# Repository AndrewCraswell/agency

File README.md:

# Agency monorepo

A Turborepo and pnpm monorepo for the agency's applications and shared packages.

## What's inside?

This Turborepo includes the following packages and apps:

### Apps and Packages

- `blog-writer`: Shopify blog-writing application
- [legislation-web](apps/legislation-web/README.md): browser product, public HTTP API and query runtime
- [legislation-ingestion](apps/legislation-ingestion/README.md): source acquisition, workers and indexing
- [legislation-mcp](apps/legislation-mcp/README.md): standalone authenticated MCP-to-HTTP adapter
- [@repo/legislation-core](packages/legislation-core/README.md): shared contracts, database schema and primitives
- `scoring`: fencing scoring application and supporting tools
- `@repo/oxlint-config`: shared [oxlint](https://oxc.rs) configuration
- `@repo/storybook-config`: shared [Storybook](https://storybook.js.org) configuration
- `@repo/typescript-config`: `tsconfig.json`s used throughout the monorepo

Applications and shared packages primarily use [TypeScript](https://www.typescriptlang.org/); legislation ingestion also
owns Python parser and scraper runtimes.

### Install dependencies

Some workspaces use `@1js` packages from the Office Azure Artifacts feed. Install dependencies normally:

```sh
pnpm install
```

If installation fails because the feed credentials have expired, refresh them and retry:

```sh
pnpm auth
pnpm install
```

For legislation setup, including local credentials after the workspace moves, see the
[runtime guide](apps/legislation-web/docs/operations/development.md). From the repository root,
`pnpm verify:legislation` runs the five-package legislation verification suite, including the diffing package.
`pnpm verify` currently delegates to that same legislation-only gate; it is not a full monorepo check. Database release
commands are owned by web and delegate to core.

### Utilities

This Turborepo has some additional tools already setup for you:

- [TypeScript](https://www.typescriptlang.org/) for static type checking
- [oxlint](https://oxc.rs) for code linting
- [oxfmt](https://oxc.rs) for code formatting
- [Vitest](https://vitest.dev) for testing
- [Lefthook](https://lefthook.dev) for Git hooks

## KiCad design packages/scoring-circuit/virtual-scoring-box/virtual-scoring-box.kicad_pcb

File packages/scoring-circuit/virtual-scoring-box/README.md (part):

# Virtual scoring box

Open `virtual-scoring-box.kicad_pro` in KiCad 10. This separate development PCB is routed and has an assembly-review
export; it has not been released to a manufacturer. The combined `../usb-scoring-platform/` design is frozen at commit
`ea7c3af023e6ad69eb4b2c7591a94a8ba3619fca`; do not change it while developing this board. Its supplier draft remains
paused.

## Product boundary

- STM32 determines foil, epee and sabre touches. The laptop displays results and controls the bout; network arrival time
  never determines contact timing. Timestamped conductor events may also be exported for development and diagnostics.
- ESP32 handles Wi-Fi/Bluetooth connectivity and the same IR remote as the future standalone model. Both processors must
  be powered in USB and wireless operation. Share firmware source and the C17 scoring core, with board-specific
  configuration.
- One USB-C port provides laptop power/data or wall-charger power for wireless use. Retain the adequately powered USB-C
  source requirement; universal USB-A adapter operation is not promised.
- Left and right enclosure-mounted ABC sockets connect by soldered wires to opposite sides of the PCB. The piste socket
  also connects by soldered wire. Provide strain relief; the piste reference is not protective earth.
- Retain accessible STM32 SWD and ESP32 programming/recovery interfaces. Same update approach as the standalone product.
- No Ethernet, Favero outputs, HUB75, audio, or high-power display supply.

## Current state and next work

The schematic contains the two acquisition circuits, STM32, ESP32, input reset-default resistors, TSOP38438 IR receiver,
and a USB-C data interface. Twenty-two standalone-only processor connections have been replaced with explicit
no-connects. J3/J4/J5 are bare PCB wire-solder terminations, excluded from the purchased-parts BOM; their provisional
1.2mm drills and wire strain relief still need assembly review. Unused copied custom symbols and header footprints have
been removed.

The native PCB has **146 footprints**, including **142 purchased components**, on a **120 x 85mm, four-layer, 1.6mm**
board. The USB interface uses GCT USB4105-GF-A, TPD2E2U06DCKR protection, a **CP2102N-A02-GQFN20R USB-to-UART bridge**,
and an **ISO7021DR serial isolator**. **TPS70933DBVR** supplies the laptop-side 3.3V rail and tolerates raw VBUS up to
30V. Its EN pin is intentionally open using the internal pull-up, never connected directly to high-voltage VBUS. C40 is
4.7uF.

`usb-power-control.kicad_sch` adds **STUSB4500QTR**, **STM32C011F6P6** and **TPS259470ARPWR**. Program and read back a
single **5V / 1.5A sink PDO** after delivery, before normal use. The eFuse provides automatic-retry current limiting,
reverse-current blocking and adjustable voltage protection. R85 sets approximately 1.21A; C54 gives approximately 25ms
for the 5V ramp. ITIMER is intentionally open for the fastest overcurrent response. Nominal UVLO is 4.04V rising / 3.69V
falling; nominal OVLO is 5.38V rising / 4.91V falling. Divider resistors are 0.1%; temperature, comparator tolerance and
fault overshoot still require review and measurement against the protected parts' limits. Raw-input capacitors are
50V-rated. R76 now senses only `USB_5V_PROTECTED`, so overvoltage removes the bridge's VBUS indication while its
controller stays powered.

**SN74LVC1G3208DBVR** implements `(USB_AWAKE OR USB_SUSPEND_EXEMPT) AND SOURCE_ALLOWED`. **SN74LVC1T45DBVR** translates
the result to protected 5V because SN6505 EN requires 0.7 times VCC. Both qualification outputs have pull-downs; R79
holds the transformer off if the translator is unpowered. An unprogrammed controller therefore cannot energize the
scoring supply. J7 is a bare primary-domain SWD pogo-pad target, not a fitted header.

The isolated processor supply is implemented and locally routed: **SN6505BDBVR**, **Wurth 750315371** 1:1.1 transformer,
two **SS14-E3/61T** rectifiers and **TPS62162DSGR** fixed-3.3V buck regulator. Both processors and the acquisition
circuits share `CORE_3V3`; the IR receiver retains its existing resistor/capacitor supply filter. The design target is
0.8A combined load, below the buck's 1A rating, not a measured whole-supply rating. The 2.2uH XAL5030-222MEC and two
10uF output capacitors follow the regulator's recommended LC range. The regulator's power-good output holds STM32 reset
low until the output is valid. A 10k output resistor provides a discharge path.

The transformer enable has a default-off pull-down. Its protected 5V input and qualified-source/suspend enable are
connected through PCB copper to the USB-C power-control section. Neither is tied directly to raw USB VBUS. USB_GND and
scoring GND remain separate, including their copper pours. The piste connection clears the supply on the front layer.
Low-input-voltage operation, radio load steps, temperature, power-down time and system insulation still need bench
verification. Component insulation ratings alone do not establish FIE compliance.

The bridge replaces the ISOUSB111. It can enumerate independently of the scoring processors and exposes `USB_AWAKE` from
its active-low suspend output. A 10k pull-down keeps this signal low while reset leaves it floating. This gives the
power circuit a hardware USB-sleep signal; it does **not** by itself qualify the source or complete the whole-board
suspend budget. The isolator defaults to UART idle-high. Pinouts, supply arrangements and the QFN land pattern were
reviewed against the rendered manufacturer drawings:
[Silicon Labs CP2102N](https://www.silabs.com/documents/public/data-sheets/cp2102n-datasheet.pdf) and
[TI ISO7021](https://www.ti.com/lit/ds/symlink/iso7021.pdf).

The laptop link is STM32 **USART2, PA2 TX / PA15 RX, AF7**, separate from USART1 to ESP32 and SWD. PA11/PA12 native USB
and the obsolete USB_PRESENT input are now explicitly unused. Desktop software needs the CP210x VCP driver and a serial
transport adapter; native STM32 USB DFU is **not connected**. Initial programming/recovery remains through SWD and the
ESP32 service header. Shared-source application updates need the board-specific serial adapter. Use framed,
sequence-numbered messages with bounded queues and flow control in the protocol; hardware RTS/CTS and USB remote wake
are not connected. The hardware bridge supports up to 3 Mbaud, but firmware throughput has not been validated.

STM32 USART1 connects directly to ESP32 on the shared 3.3V rail: `STM_TX` to ESP RX and `STM_RX` to ESP TX. Same-rail
translators U10/U11 and their redundant C23-C26/R30/R31 support were removed. R72/R73 retain idle-high reset defaults;
C22/C27 remain at the ESP32 supply. The removed parts' copper, custom symbol and footprint were also removed.

All schematic connections are routed. In1.Cu contains only the separate scoring and USB ground planes: all 33 former
power-track segments on that layer were removed. In2.Cu carries the corresponding 3.3V regions and ordinary signal
routes. Raw VBUS and protected 5V retain separate back-layer pours and explicit eFuse input/output joins. The USB bridge
and protection device face the connector directly. Both data nets have two vias for the short USB-C duplicated-contact
joins; the main data routes remain on the front. The back joins have a local, stitched USB-ground reference on In2.Cu.
Local via antipads remain; this is not a measured USB-compliance result.

The regulator, inductor and output capacitors form a compact group with a direct top-layer ground return. Output sensing
is separated from the switching node. Y1 and its load capacitors sit beside the STM32 oscillator pins: both crystal nets
stay on the front, with no vias and 6.90/9.48mm total drawn HSE_IN/HSE_OUT copper, including capacitor branches.

The placement refinement puts J2 beside STM32 and J6 beside ESP32, with the ESP reset/boot buttons grouped beside J6.
The seven input-load resistors sit beside their STM32 pins; repeated driver/default resistors form orderly local rows.
Twenty-five components moved relative to `f9809c1`; all 146 footprint identities, values and pad/net assignments are
unchanged. External connectors, board outline, ESP32 antenna position, USB data, crystal and switching-loop geometry
remain unchanged. In1.Cu still has no signal or power tracks. The antenna extends beyond the top edge; the final
enclosure must leave it clear.

The surface-routing pass preserves every component position and pad/net assignment. **LEFT_A, LEFT_C, RIGHT_A, RIGHT_B,
RIGHT_C and PISTE** now run entirely on F.Cu. LEFT_B retains its shorter front/back path; forcing it onto the front
produced an excessive detour. Four control networks no longer use In2.Cu: LEFT_C_DRIVE, RIGHT_C_DRIVE, PISTE_OE_N and
SWDIO. Tight processor escapes remain internal where a front-only path would be obstructed or longer. The reset button
has a short, dedicated connection to the scoring ground plane. Redundant signal vias were removed.

Relative to the preceding branding checkpoint, In2.Cu track length falls from **772.930mm to 681.571mm** (11.8%); its
share of total track length falls from **24.2% to 21.4%**. F.Cu carries 1472.575mm and B.Cu 1029.816mm. Total drawn
track length is **3183.962mm**, down from 3198.362mm; there are **1618 segments and 366 vias**, down from 1629 and 377.
In1.Cu remains ground-plane-only. These are CAD measurements, not propagation delays, measured electrical performance,
or proof of a globally optimal layout. Shorter aggregate routing does not mean every individual net is shorter.

White silkscreen identifies STM32, ESP32, the IR receiver, left/right inputs, USB-C, piste, A/B/C wire pads, service
headers and reset/boot controls. J2/J6 have individual pin labels. The product marking is **FENCING CLUB**, **VIRTUAL
SCORING BOX**, and **USB + WIRELESS**. The piste termination says only **PISTE**; the electrical safety distinction
remains in this documentation. Omit code-only component labels and lookup legends from the silkscreen; full component
references remain on the fabrication drawing. Text meets the enabled 0.8mm minimum and clears solder pads and board
edges. Provide an actual KiCad 3D render with each board-update checkpoint.

The native stackup now specifies [JLC04161H-3313](https://jlcpcb.com/impedance): nominal 1.6mm four-layer construction,
35um outer / 15.2um inner copper, 0.0994mm outer prepregs (Dk 4.1), and a 1.265mm core (Dk 4.6). Select this exact
stackup in the fabrication draft. Do not substitute the default 7628 stackup silently. On 2026-09-14,
[JLCPCB's calculator](https://jlcpcb.com/pcb-impedance-calculator) returned 0.1862mm width for 90 ohms and 0.2007mm for
86 ohms at the main run's 1.10mm edge spacing, L1 over L2, non-coplanar, with solder mask. The actual 0.20mm traces are
therefore approximately 86 ohms nominal. At the short 0.30mm-gap approach, the calculator returned 0.1969mm for 83 ohms.
Retain the existing geometry; these uniform-cross-section estimates do not model pads, vias, connector stubs or
manufacturing tolerance. They are not a measured USB-compliance result. Review the selected stackup in the production
files and test the assembled full-speed USB link during bring-up.

1. Finish the primary-side sleep-current and voltage/current tolerance review, then verify antenna clearance and
   connector access. The virtual-board source-control configuration is implemented and host-tested; its physical power
   behavior is not measured. Board size is not frozen; the old 165 x 100mm layout is not this product.
2. Complete supplier matching, placement orientation and assembly/programming acceptance using this board's export, not
   the combined board's paused order. All 142 purchased parts have manufacturer/MPN/footprint fields and matching
   placement rows. All purchased components have resolvable package models. The bare solder/pogo targets have no model
   and are excluded from both BOM and placement. Use the revised J2/J6 locations when reviewing programming fixtures.
3. Implement the board-specific STM32 serial adapter/shared application firmware, then validate real power, input
   thresholds, USB and wireless behavior on assembled hardware before use with fencers. Application development does not
   require the physical PCB, but successful host tests alone cannot qualify an assembled scoring machine.

USB data-interface placement, the isolated power stage, source-control hardware/firmware and PCB routing are
implemented; assembly release and physical qualification are not complete. Preserve the existing compatibility promise
of advertised Type-C current at least 1.5A **or** a qualified 5V/1.5A PD contract unless the user approves narrowing it.
A direct-current-advertisement-only design could omit PD negotiation and the separate power-control processor, but that
is an unapproved compatibility change, not the current specification. The smaller supply must power both STM32 and
ESP32; the combined board's STM32-only laptop budget is insufficient. Do not suppress pending power/connection findings.
No new document/evidence validators or firmware forks are needed.

The power firmware must combine source qualification with the bridge's sleep signal: no qualified source means the
scoring supply stays off; a source requiring USB suspend allows it only while USB is awake. Qualified sources exempt
from USB suspend, including an appropriate wall charger, must support wireless operation without USB enumeration.
Preserve the existing 5V PD compatibility; do not substitute a direct-Type-C-only policy. The hardware gate is routed
and the shared [power-controller source](../../../apps/scoring/firmware/power-control/README.md) now builds a
virtual-board image. PA4 outputs SOURCE_ALLOWED, PA5 outputs USB_SUSPEND_EXEMPT. PD alert, eFuse fault, USB_AWAKE and a
nominal 32ms RTC alarm wake Stop0. A requested RDO exemption alone is not permission; the firmware checks the fresh
source flags. The virtual image never enables the combined board's 20V/display profile. After delivery, program U24
using the virtual image, not the combined image, and configure/read back U23's single 5V/1.5A NVM PDO separately.

## Current checkpoint checks

KiCad contains **146 components**, including four bare wire/service targets. ERC reports **zero findings**. Native DRC
reports **zero violations**, **zero schematic/PCB parity issues**, and **zero unconnected items**. Unused routing tails
were removed. The rule floor is **0.15mm track / 0.15mm clearance**, with wider ordinary routes and power copper. This
is above [JLCPCB's published multilayer 1oz trace/space minimum](https://jlcpcb.com/capabilities/Capab); it does not
waive isolation, current-carrying capacity or assembly review. Local 0.5mm vias use 0.25mm drills. An edge-specific
ESP32 footprint clips only off-board silkscreen; its pads, manufacturer model and antenna keepout are unchanged. The
0.2mm minimum drill matches the retained ESP32 thermal-via footprint and the combined board's existing fabrication
constraint; it is not a waiver of assembly review.

The native custom rule also passes a **2mm minimum copper-clearance screen** between primary USB/power/control nets and
scoring-side nets, including intentionally unconnected primary package pads. This is an engineering layout floor, not a
FIE requirement, dielectric test, interlayer insulation rating or measured surface-creepage result. Physical insulation
qualification remains separate from ordinary PCB DRC.

The manufacturing exporter includes fresh `board-top-3d.png` and `board-bottom-3d.png` renders in its output directory.
Generated reports and images are local, ignored outputs. This is a clean native CAD/assembly-export checkpoint, not a
firmware release, bench result or permission to order. U22 uses the installed KiCad WSON-8 2x2mm, 0.5mm-pitch package
model; its obsolete `Texas_DSG0008A_` model filename was corrected without changing its footprint or placement.

The CP2102N footprint uses KiCad's Silicon Labs QFN20 land pattern and a retained, unmodified
[KiCad StepUp package model](https://gitlab.com/kicad/libraries/kicad-packages3D/-/blob/6.0.11/Package_DFN_QFN.3dshapes/SiliconLabs_QFN-20-1EP_3x3mm_P0.5mm.step).
The model retains its copyright and CC BY-SA 4.0 notice with the KiCad electronic-design exception. It is a package
model, not a manufacturer assembly approval.

T1 uses Wurth's exact manufacturer symbol, footprint and STEP model from the
[WE-PPTI product library](https://www.we-online.com/en/components/products/WE-PPTI?sq=750315371), with only local
library/model paths changed. Its six-pad land pattern and pin ordering were checked against the rendered
[750315371 drawing](https://www.we-online.com/components/products/datasheet/750315371.pdf). The converter was checked
against [SN6505B](https://www.ti.com/lit/ds/symlink/sn6505b.pdf),
[TPS62162](https://www.ti.com/lit/ds/symlink/tps62162.pdf) and [SS14](https://www.vishay.com/docs/88746/ss12.pdf)
manufacturer documentation. Supply, distribution and reset/enable connections have no remaining native connectivity
findings. Physical startup, fault, suspend, load-step and temperature tests remain necessary.

Source-control pin/function review uses [STUSB4500](https://www.st.com/resource/en/datasheet/stusb4500.pdf),
[STM32C011](https://www.st.com/resource/en/datasheet/stm32c011f4.pdf),
[TPS25947](https://www.ti.com/lit/ds/symlink/tps25947.pdf), [TPS709](https://www.ti.com/lit/ds/symlink/tps709.pdf),
[OR-AND gate](https://www.ti.com/lit/ds/symlink/sn74lvc1g3208.pdf) and
[enable translator](https://www.ti.com/lit/ds/symlink/sn74lvc1t45.pdf). The eFuse uses the correct ten-pin RPW model
[provided by TI](https://e2e.ti.com/support/power-management-group/power-management/f/power-management-forum/982334/tps25947-step-file),
not the unrelated twenty-pin download reported in that thread. Its STEP assembly already supplies the seating transform;
no extra rotation or height offset is applied.

## Assembly handoff

Run `./export-manufacturing.ps1` with KiCad 10 and LLVM/Clang available. It creates a new output directory, runs native
ERC/DRC/parity checks, exports the exact BOM and matching placements, Gerbers, plated/non-plated drills and an assembly
PDF, and builds the **virtual** U24 image from current source. Gerbers, drills and placements share the lower-left
auxiliary origin (board coordinates 50,135mm); exported component positions use positive X/Y millimetres. The four
copper layers are F.Cu, In1.Cu, In2.Cu, B.Cu. Minimum drill is 0.2mm; the USB shell uses plated slots. Request standard
green solder mask and white silkscreen for this prototype. A 3D colour is not a manufacturing order option.

- Fit all 142 BOM parts, including through-hole J2/J6 and U13. Do not substitute parts or rotate them from generic
  catalog previews without checking pin 1 against the native pad map. The Gerber ZIP is bare-board data, not assembly
  instructions; send BOM, placement and programming requirements separately when an order is authorized.
- J3/J4/J5 are seven bare 1.2mm plated wire holes. J7 is five bare primary-domain SWD pads. Do not buy or fit connectors
  at these references. Enclosure-mounted ABC/piste sockets, wire gauge, harness length and strain relief are not defined
  by the PCB BOM. Keep left/right wiring distinct. Leave clearance around the USB cable, IR window and ESP32 antenna.
- Program/read back **U24 STM32C011** through J7 with the included `programming/U24/power-control.hex`. Use USB_GND for
  this primary-side probe and do not inject voltage through its reference pin. Configure/read back **U23 STUSB4500** NVM
  for one 5V/1.5A sink PDO using ST's programming procedure. Volatile runtime configuration is not a factory NVM image.
  This is post-delivery bring-up work, not a prerequisite for the prototype assembly order. See the procedure below; do
  not describe an unprogrammed board as ready to run the scoring application.
- J2 is the isolated STM32 scoring MCU's SWD; J6 is ESP32 3.3V UART recovery. Do not bridge their scoring GND to USB_GND
  with non-isolated programming equipment during isolation tests. No complete virtual-box scoring/application image is
  included yet; the combined STM32 image's PA2 output configuration is not the virtual USART2 adapter.
- After assembly, test cold-start, source changes, USB suspend/resume, rejected low-power sources, fault shutdown, radio
  load steps, temperatures, acquisition thresholds and insulation before connecting fencers. Factory electrical
  continuity and host software tests do not replace these measurements.

The primary-side suspend review is not a worst-case compliance proof. TPS25947 specifies 610uA maximum on-state
quiescent current; CP2102N gives 195uA **typical**, excluding USB pull-up current; STUSB4500's 210uA maximum is for
**unattached/no communication**, not an active PD session. STM32C011 Stop current, LSI/RTC/watchdog overhead, wake duty,
resistor dividers and bus pull-ups must also be included. In particular, a stuck-low PD alert can prevent Stop. Measure
the complete input current under the source's actual suspend policy; do not add typical values and label the sum a
guaranteed limit. References: [CP2102N](https://www.silabs.com/documents/public/data-sheets/cp2102n-datasheet.pdf),
[STUSB4500 table 22](https://www.st.com/resource/en/datasheet/stusb4500.pdf),
[STM32C011 table 31](https://www.st.com/resource/en/datasheet/stm32c011f4.pdf),
[TPS25947](https://www.ti.com/lit/ds/symlink/tps25947.pdf).

### JLCPCB validation draft

The [current virtual-box draft](https://cart.jlcpcb.com/smt-order/?pcbFileNo=0d7e87fc3bcf4669aeb7055e406425c1) is
**unsubmitted and unpaid**. On 2026-09-14 it accepted the revised BOM and matching placement file from
`output/manufacturing-20260914-051026/`: **142 purchased references, 140 confirmed, two inventory shortages**. No
required component was omitted. J1 USB4105-GF-A/C3020560 was explicitly reselected after the upload left its quantity at
zero; the corrected draft has two fitted USB connectors, one per assembled board.

The procurement-only update changes 23 component identities, with no change to values, nets, footprints, component
positions or copper. The Gerbers already loaded from `output/assembly-surface-routing/` remain geometrically valid. The
latest export also contains matching Gerbers, 142 BOM/placement rows, an assembly PDF and native top/bottom 3D renders.
ERC, DRC, unconnected and schematic/PCB parity findings are all zero under the enabled rules. The virtual U24 image
cross-builds to 3096 bytes code / 72 bytes RAM. These are CAD/software checks, not physical qualification.

Order configuration remains five bare boards and two fully assembled boards: Standard PCBA, all components on top, 120 x
85mm, 1.6mm four-layer FR-4, green mask, white legend, ENIG, 1oz outer / 0.5oz inner copper and **JLC04161H-3313**.
Copper order is F.Cu / In1.Cu / In2.Cu / B.Cu. Two 5mm rails and depaneling are selected. Fill/cap only the
0.2/0.25/0.3mm via groups, not connector, wire or locating holes. Keep production-file and placement confirmation
required, with automatic confirmation disabled. Final supplier placement inspection is still pending.

#### Stocked replacements

| References                            | Current MPN         | JLCPCB part |
| ------------------------------------- | ------------------- | ----------- |
| C1, C15, C21, C33, C39, C49, C50, C52 | CC0603KRX7R9BB105   | C559769     |
| C12                                   | CC0603KRX7R9BB103   | C100042     |
| C14                                   | C1608X7S1A475KT000E | C342959     |
| C17, C18                              | CC0603JRNPO9BN270   | C107045     |
| C22                                   | C1608X5R1C106MT000N | C342854     |
| C41-C46                               | C3216X7R1C106KT000N | C342827     |
| J2                                    | HTSW-105-07-G-S     | C3337223    |
| J6                                    | HTSW-106-07-G-S     | C3334125    |
| R81                                   | RT0603BRD0723K7L    | C861245     |
| R83                                   | RT0603BRD0734K8L    | C861338     |

The capacitors and headers reuse the standalone board's reviewed selections. Yageo replacements retain the required
capacitance, dielectric, tolerance and package; the TDK parts use the current ordering identities. J2/J6 retain their
pitch, pin length, footprint and pinout; `-G` changes the contact/tail plating, not connector geometry. Both still
require through-hole assembly.

The [1uF/50V Yageo specification](https://yageogroup.com/download/specsheet/CC0603KRX7R9BB105) was also checked against
the laptop-specific rails: C49 at 1.2V, C50 at 2.7V, and the 3.3V nodes. The typical DC-bias plot loses about 10% at
2.7V; combining that estimate with initial tolerance and X7R temperature variation leaves approximately 0.67uF against
STUSB4500's 0.5uF minimum on VREG_2V7. This is a design estimate, not an aged worst-case guarantee. At high raw VBUS, do
not assume the full marked 1uF remains effective.

R81/R83 retain 23.7k/34.8k, 0.1%, 25ppm/C, 100mW, 75V and 0603. The
[Yageo RT datasheet](https://yageogroup.com/content/datasheet/asset/file/pyu-rt_1-to-0-01_rohs_l), ordering table and
RT0603 rating table support these exact configurations. The eFuse's nominal voltage thresholds are unchanged. Native
MPN/catalog fields are the source of the BOM's `LCSC Part #` column; inspect every match after an upload.

#### Remaining sourcing and order steps

| Reference | Exact part                      | Current gap                                              | Prepared procurement                                                                                                 |
| --------- | ------------------------------- | -------------------------------------------------------- | -------------------------------------------------------------------------------------------------------------------- |
| T1        | Wurth 750315371 / C5184247      | Five-piece total requirement, five short                 | Five from Element14_UK at $3.6257 each; $18.13 plus $0.91 displayed duty; 2,819 listed in stock, 10-15 business days |
| U26       | TI SN74LVC1G3208DBVR / C2682152 | Five-piece total requirement, two at JLCPCB, three short | Five exact TI parts at $0.338 each, $1.69 total; 6,000 listed in stock, 10-14 business days                          |

These two exact-part lines are saved in the
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
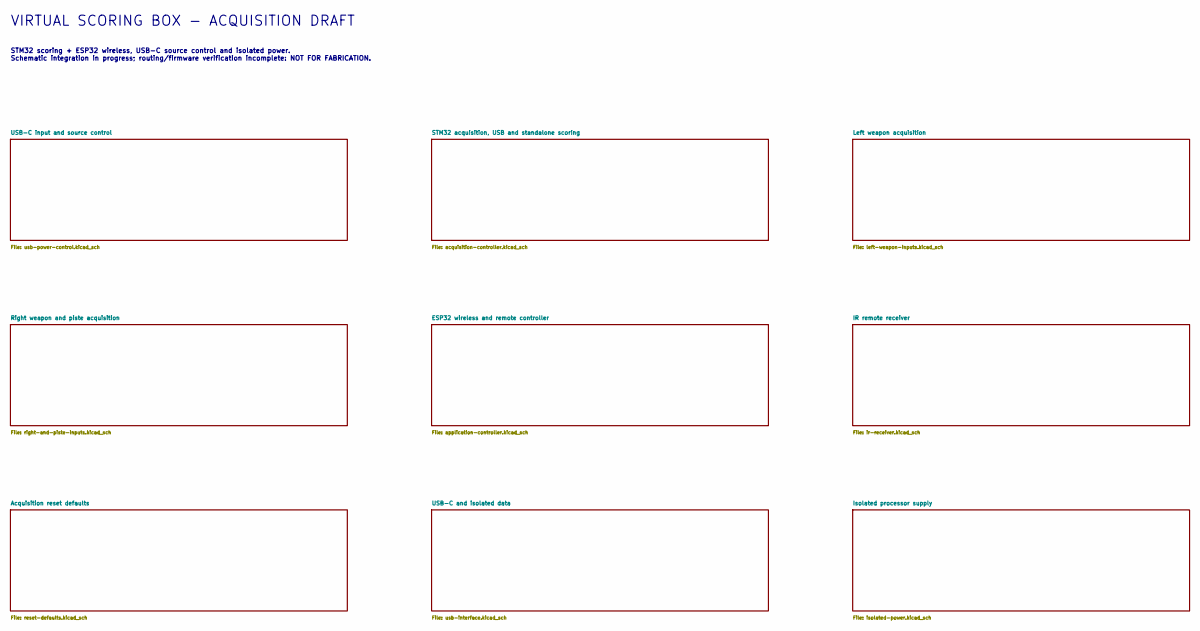
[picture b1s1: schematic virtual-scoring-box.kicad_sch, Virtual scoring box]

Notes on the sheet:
VIRTUAL SCORING BOX - ACQUISITION DRAFT
STM32 scoring + ESP32 wireless, USB-C source control and isolated power. Schematic integration in progress; routing/firmware verification incomplete: NOT FOR FABRICATION.

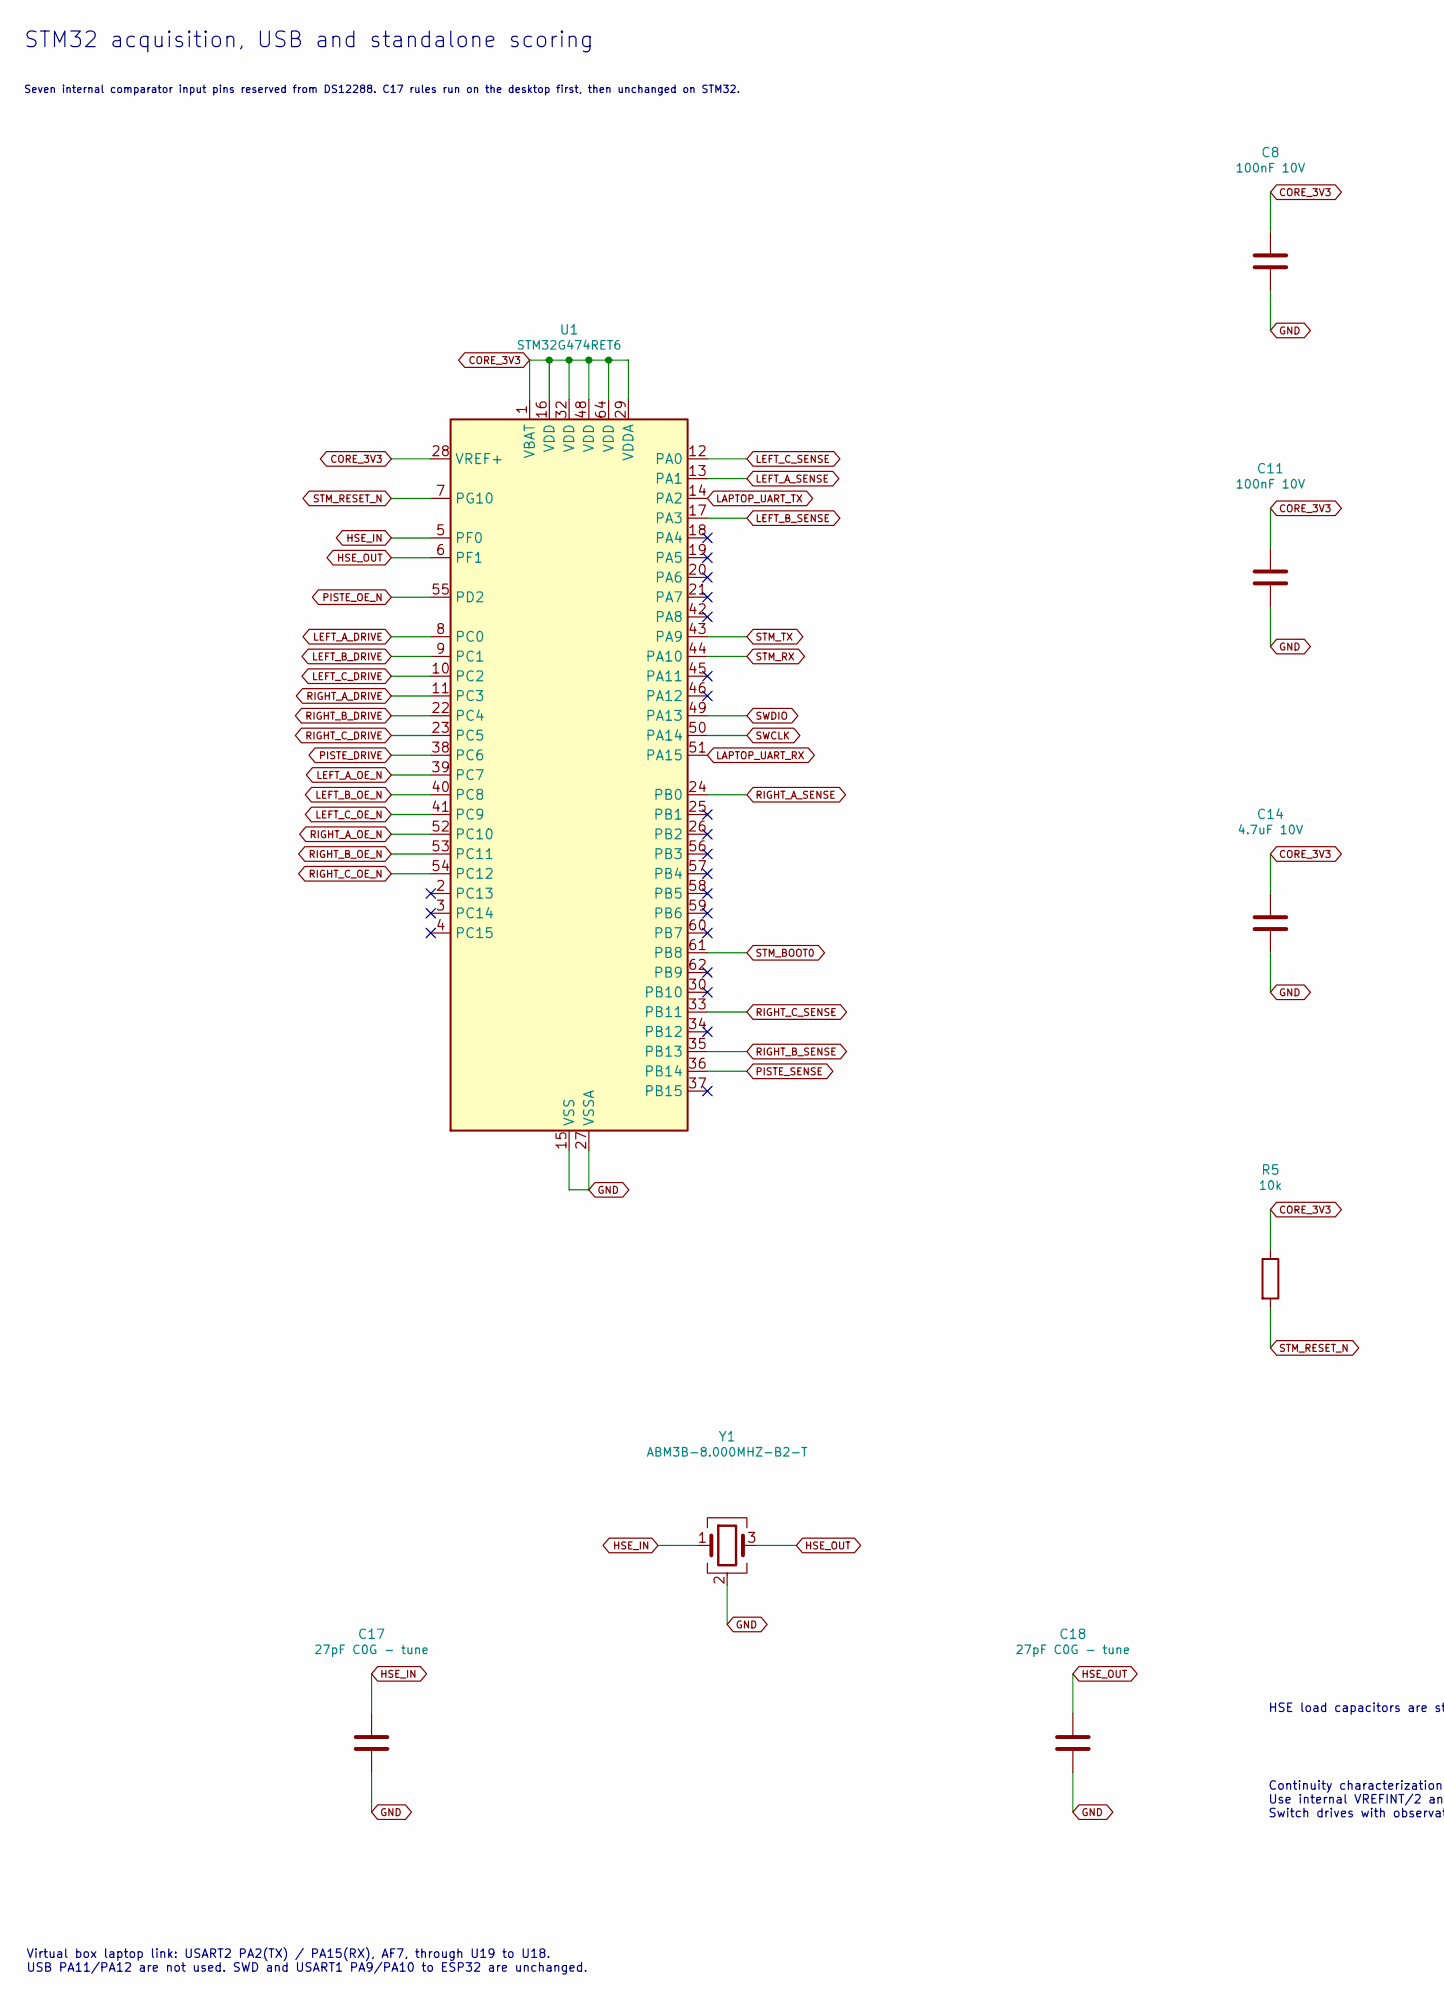
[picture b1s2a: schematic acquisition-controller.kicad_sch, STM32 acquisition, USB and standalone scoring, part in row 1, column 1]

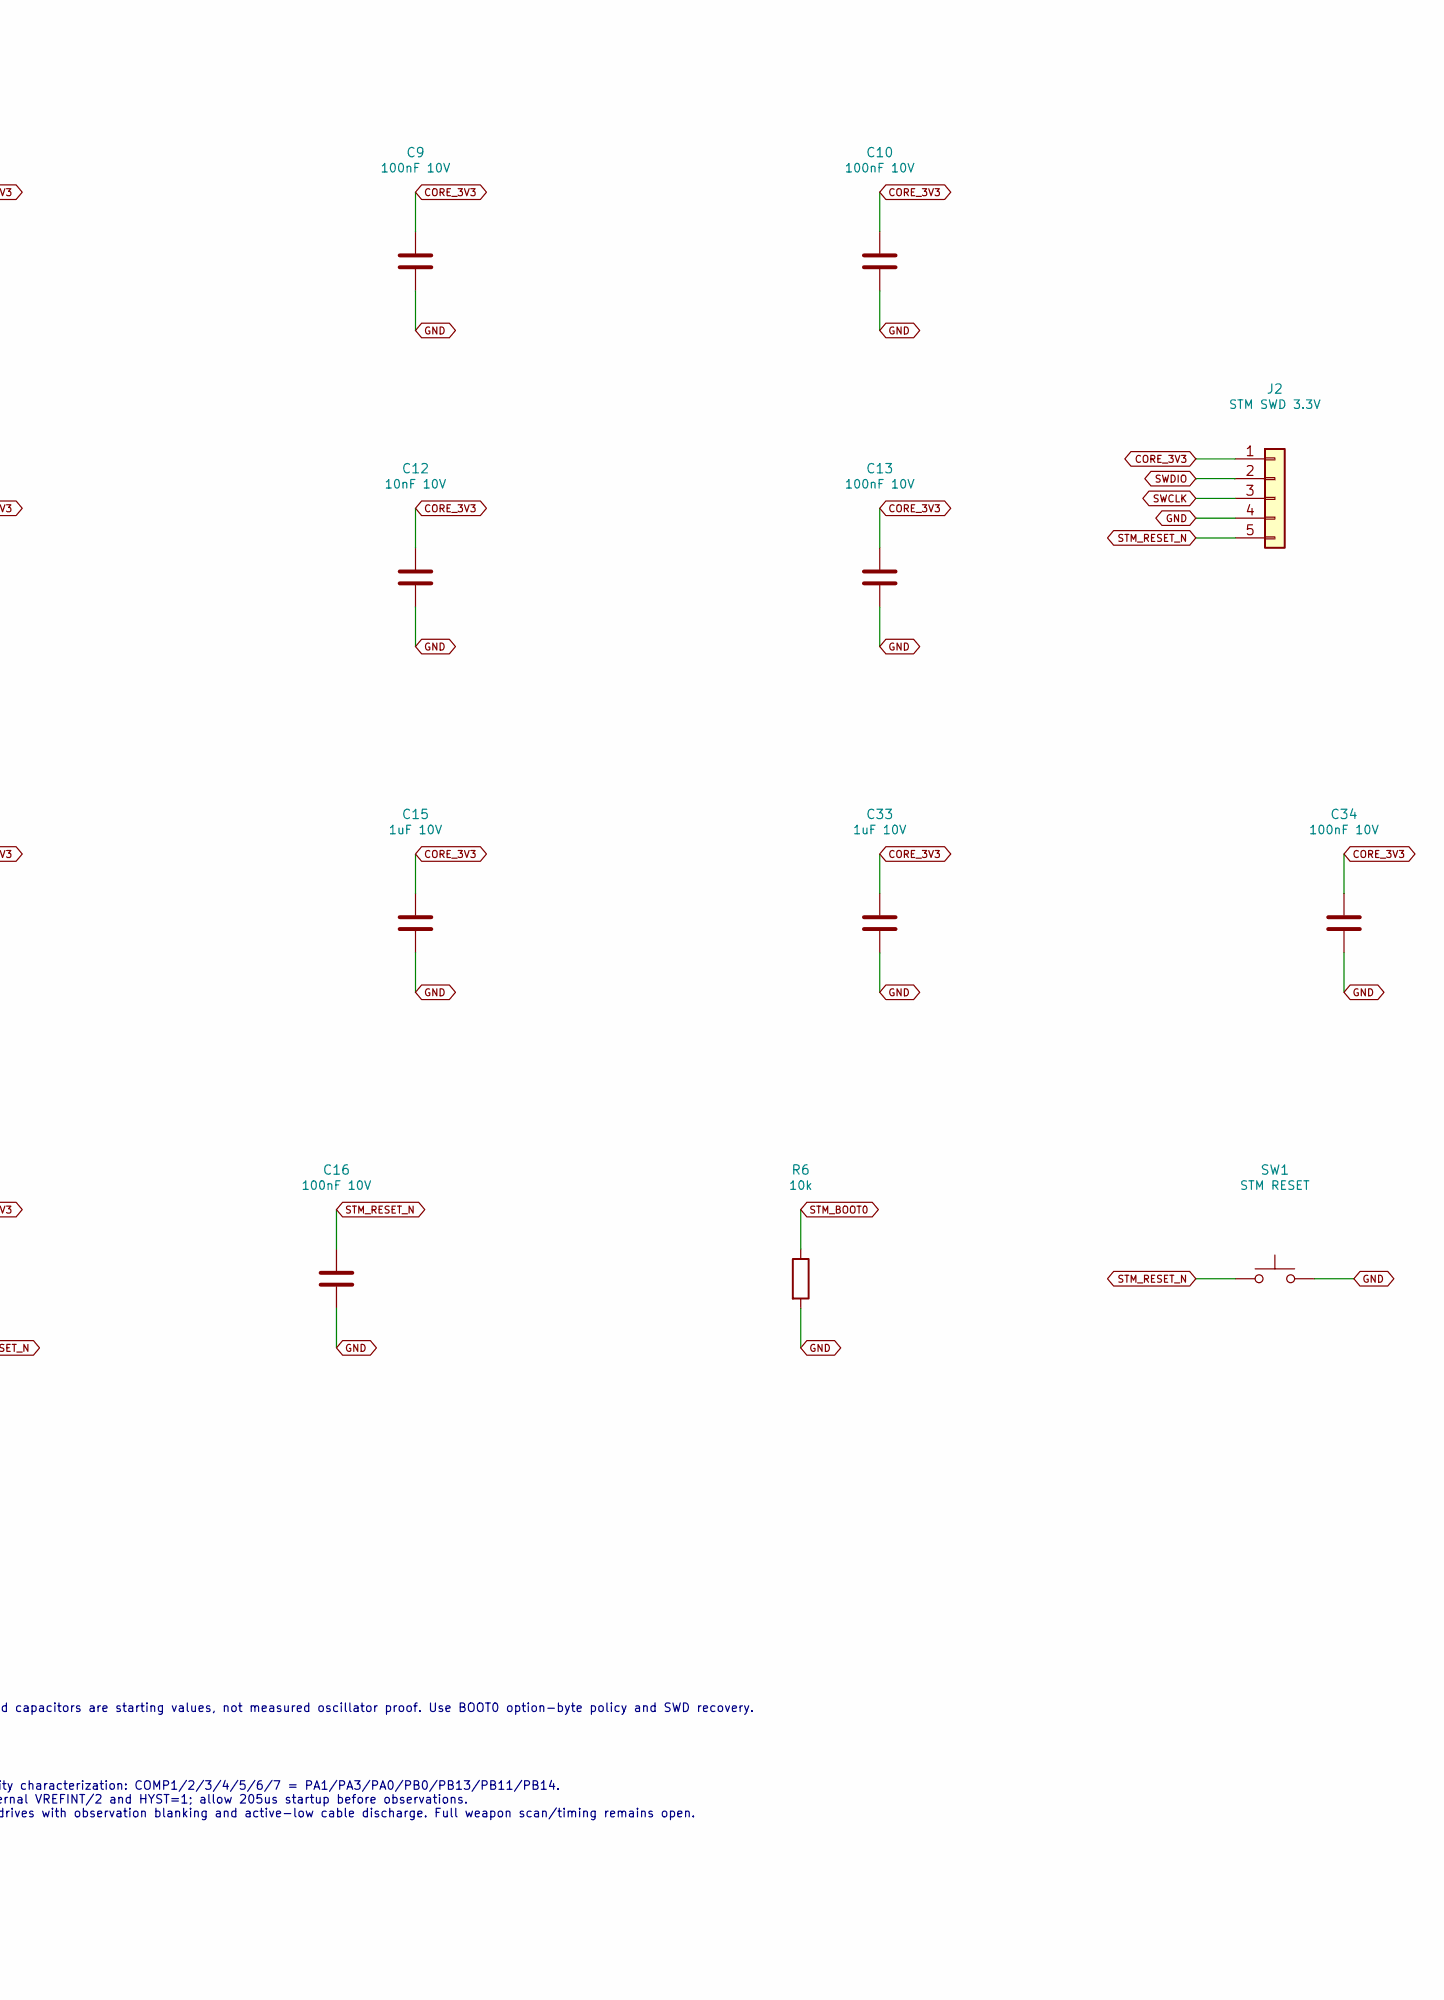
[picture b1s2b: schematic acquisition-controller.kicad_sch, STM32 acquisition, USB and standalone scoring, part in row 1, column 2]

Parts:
C8, C9, C10, C11, C13, C16, C34: 100nF 10V; C_0603_1608Metric; MPN CC0603KRX7R9BB104
C12: 10nF 10V; C_0603_1608Metric; MPN CC0603KRX7R9BB103; JLCPCB C100042
C14: 4.7uF 10V; C_0603_1608Metric; MPN C1608X7S1A475KT000E; JLCPCB C342959
C15, C33: 1uF 10V; C_0603_1608Metric; MPN CC0603KRX7R9BB105; JLCPCB C559769
C17, C18: 27pF C0G - tune; C_0603_1608Metric; MPN CC0603JRNPO9BN270; JLCPCB C107045
J2: STM SWD 3.3V; Samtec_HTSW-105-07-L-S; MPN HTSW-105-07-G-S; JLCPCB C3337223
R5, R6: 10k; R_0603_1608Metric; MPN RC0603FR-0710KL
SW1: STM RESET; SW_SPST_TL3342; MPN TL3342F160QG
U1: STM32G474RET6; LQFP-64_10x10mm_P0.5mm; MPN STM32G474RET6
Y1: ABM3B-8.000MHZ-B2-T; Crystal_SMD_Abracon_ABM3B-4Pin_5.0x3.2mm; MPN ABM3B-8.000MHZ-B2-T

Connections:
CORE_3V3: C8.1, C9.1, C10.1, C11.1, C12.1, C13.1, C14.1, C15.1, C33.1, C34.1, J2.1, R5.1, U1.1 (VBAT), U1.16 (VDD), U1.28 (VREF+), U1.29 (VDDA), U1.32 (VDD), U1.48 (VDD), U1.64 (VDD); also elsewhere on the board
GND: C8.2, C9.2, C10.2, C11.2, C12.2, C13.2, C14.2, C15.2, C16.2, C17.2, C18.2, C33.2, C34.2, J2.4, R6.2, SW1.2, U1.15 (VSS), U1.27 (VSSA), U1.31 (VSS), U1.47 (VSS), U1.63 (VSS), Y1.2 (G), Y1.4 (G); also elsewhere on the board
HSE_IN: C17.1, U1.5 (PF0), Y1.1
HSE_OUT: C18.1, U1.6 (PF1), Y1.3
LAPTOP_UART_RX: U1.51 (PA15); also elsewhere on the board
LAPTOP_UART_TX: U1.14 (PA2); also elsewhere on the board
LEFT_A_DRIVE: U1.8 (PC0); also elsewhere on the board
LEFT_A_OE_N: U1.39 (PC7); also elsewhere on the board
LEFT_A_SENSE: U1.13 (PA1); also elsewhere on the board
LEFT_B_DRIVE: U1.9 (PC1); also elsewhere on the board
LEFT_B_OE_N: U1.40 (PC8); also elsewhere on the board
LEFT_B_SENSE: U1.17 (PA3); also elsewhere on the board
LEFT_C_DRIVE: U1.10 (PC2); also elsewhere on the board
LEFT_C_OE_N: U1.41 (PC9); also elsewhere on the board
LEFT_C_SENSE: U1.12 (PA0); also elsewhere on the board
PISTE_DRIVE: U1.38 (PC6); also elsewhere on the board
PISTE_OE_N: U1.55 (PD2); also elsewhere on the board
PISTE_SENSE: U1.36 (PB14); also elsewhere on the board
RIGHT_A_DRIVE: U1.11 (PC3); also elsewhere on the board
RIGHT_A_OE_N: U1.52 (PC10); also elsewhere on the board
RIGHT_A_SENSE: U1.24 (PB0); also elsewhere on the board
RIGHT_B_DRIVE: U1.22 (PC4); also elsewhere on the board
RIGHT_B_OE_N: U1.53 (PC11); also elsewhere on the board
RIGHT_B_SENSE: U1.35 (PB13); also elsewhere on the board
RIGHT_C_DRIVE: U1.23 (PC5); also elsewhere on the board
RIGHT_C_OE_N: U1.54 (PC12); also elsewhere on the board
RIGHT_C_SENSE: U1.33 (PB11); also elsewhere on the board
STM_BOOT0: R6.1, U1.61 (PB8)
STM_RESET_N: C16.1, J2.5, R5.2, SW1.1, U1.7 (PG10); also elsewhere on the board
STM_RX: U1.44 (PA10); also elsewhere on the board
STM_TX: U1.43 (PA9); also elsewhere on the board
SWCLK: J2.3, U1.50 (PA14)
SWDIO: J2.2, U1.49 (PA13)

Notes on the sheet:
HSE load capacitors are starting values, not measured oscillator proof. Use BOOT0 option-byte policy and SWD recovery.
Continuity characterization: COMP1/2/3/4/5/6/7 = PA1/PA3/PA0/PB0/PB13/PB11/PB14. Use internal VREFINT/2 and HYST=1; allow 205us startup before observations. Switch drives with observation blanking and active-low cable discharge. Full weapon scan/timing remains open.
STM32 acquisition, USB and standalone scoring
Seven internal comparator input pins reserved from DS12288. C17 rules run on the desktop first, then unchanged on STM32.
Virtual box laptop link: USART2 PA2(TX) / PA15(RX), AF7, through U19 to U18. USB PA11/PA12 are not used. SWD and USART1 PA9/PA10 to ESP32 are unchanged.

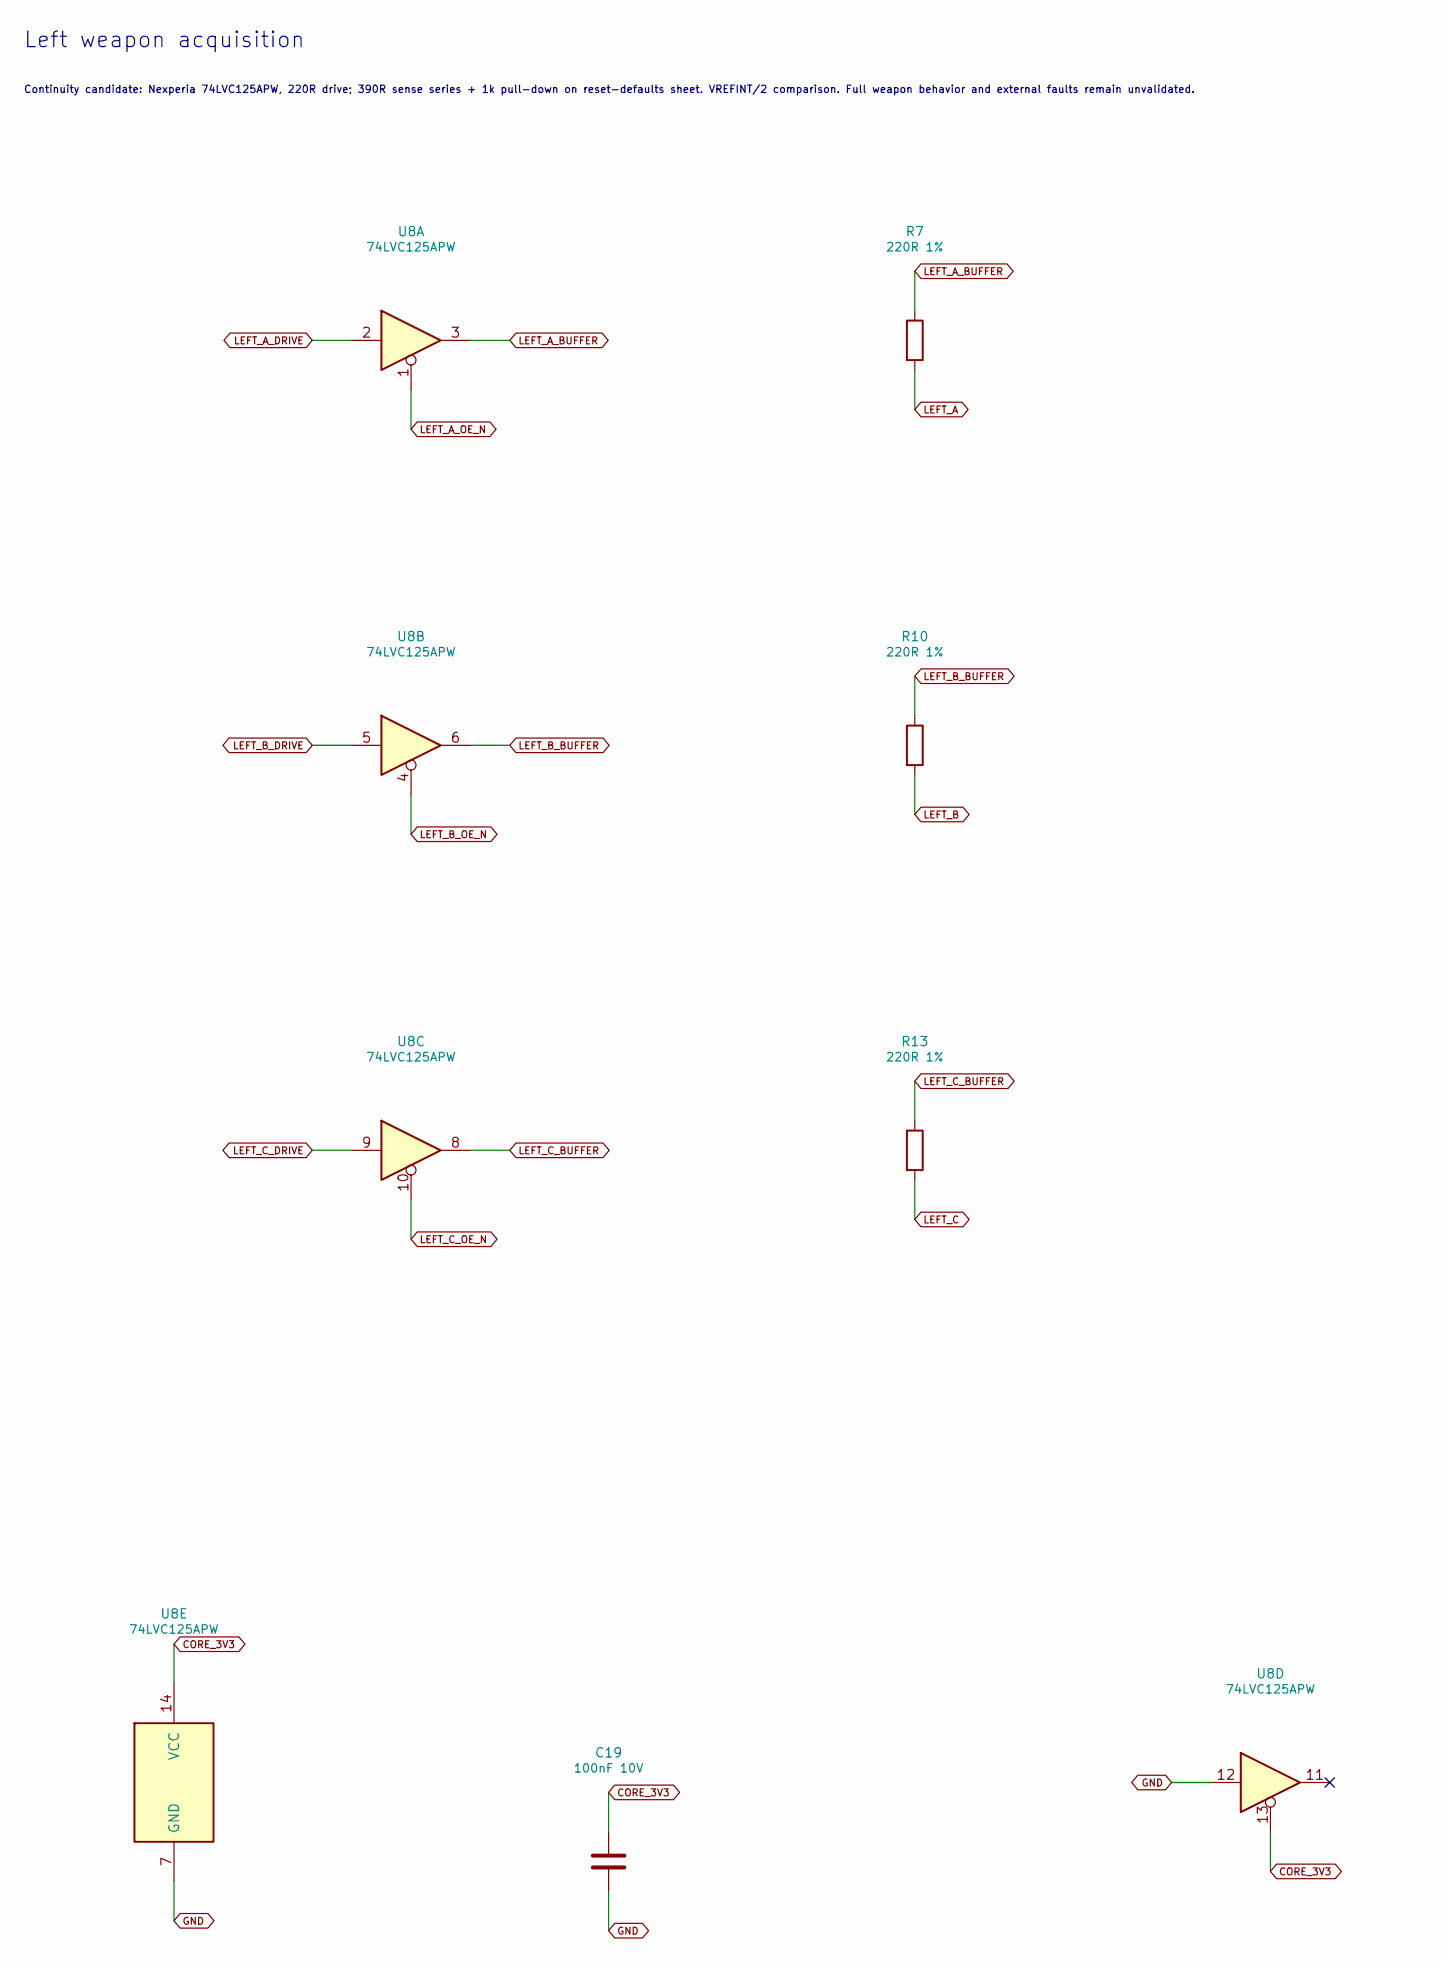
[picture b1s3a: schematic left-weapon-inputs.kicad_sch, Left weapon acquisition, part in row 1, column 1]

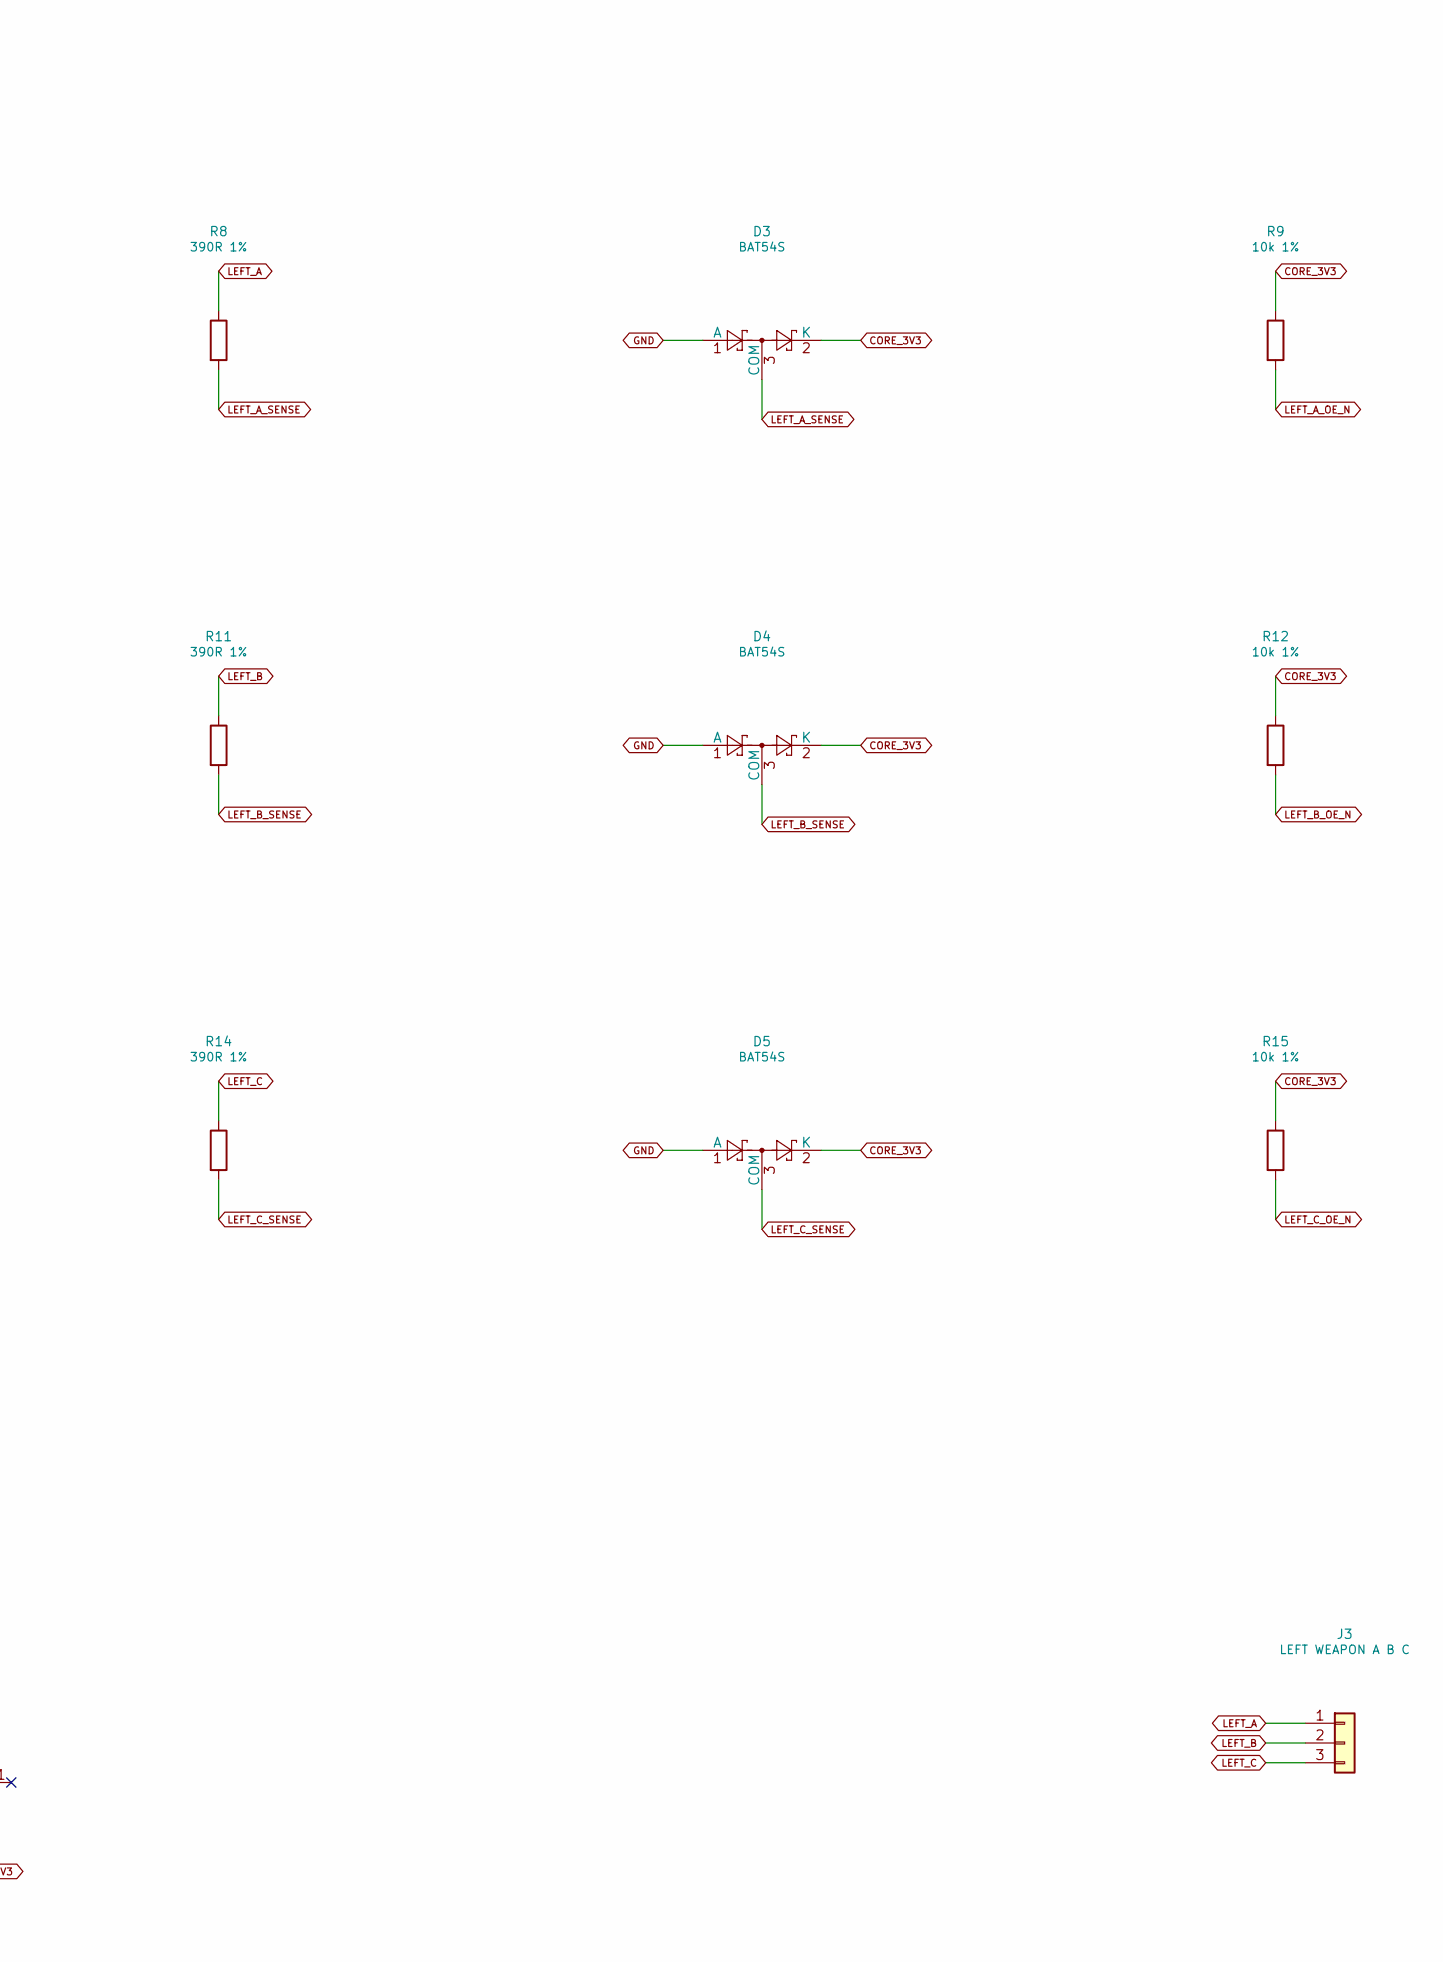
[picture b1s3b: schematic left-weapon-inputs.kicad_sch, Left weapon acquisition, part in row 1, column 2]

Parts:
C19: 100nF 10V; C_0603_1608Metric; MPN CC0603KRX7R9BB104
D3, D4, D5: BAT54S; SOT-23; MPN BAT54S,215
J3: LEFT WEAPON A B C; Wire_Solder_3; MPN PCB solder termination
R7, R10, R13: 220R 1%; R_0603_1608Metric; MPN ERJPA3F2200V
R8, R11, R14: 390R 1%; R_0603_1608Metric; MPN RC0603FR-07390RL
R9, R12, R15: 10k 1%; R_0603_1608Metric; MPN RC0603FR-0710KL
U8: 74LVC125APW; TSSOP-14_4.4x5mm_P0.65mm; MPN 74LVC125APW,118

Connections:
CORE_3V3: C19.1, D3.2 (K), D4.2 (K), D5.2 (K), R9.1, R12.1, R15.1, U8.13, U8.14 (VCC); also elsewhere on the board
GND: C19.2, D3.1 (A), D4.1 (A), D5.1 (A), U8.7 (GND), U8.12; also elsewhere on the board
LEFT_A: J3.1, R7.2, R8.1
LEFT_A_BUFFER: R7.1, U8.3
LEFT_A_DRIVE: U8.2; also elsewhere on the board
LEFT_A_OE_N: R9.2, U8.1; also elsewhere on the board
LEFT_A_SENSE: D3.3 (COM), R8.2; also elsewhere on the board
LEFT_B: J3.2, R10.2, R11.1
LEFT_B_BUFFER: R10.1, U8.6
LEFT_B_DRIVE: U8.5; also elsewhere on the board
LEFT_B_OE_N: R12.2, U8.4; also elsewhere on the board
LEFT_B_SENSE: D4.3 (COM), R11.2; also elsewhere on the board
LEFT_C: J3.3, R13.2, R14.1
LEFT_C_BUFFER: R13.1, U8.8
LEFT_C_DRIVE: U8.9; also elsewhere on the board
LEFT_C_OE_N: R15.2, U8.10; also elsewhere on the board
LEFT_C_SENSE: D5.3 (COM), R14.2; also elsewhere on the board

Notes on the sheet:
Left weapon acquisition
Continuity candidate: Nexperia 74LVC125APW, 220R drive; 390R sense series + 1k pull-down on reset-defaults sheet. VREFINT/2 comparison. Full weapon behavior and external faults remain unvalidated.

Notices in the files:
apps/scoring/docs/specifications/boards/open-piste/upstream/ESP32ScoringDevice_PCB_THT_Rev1.2.kicad_pcb:
©Piet Wauters 2024 GNU GPL V3.0
